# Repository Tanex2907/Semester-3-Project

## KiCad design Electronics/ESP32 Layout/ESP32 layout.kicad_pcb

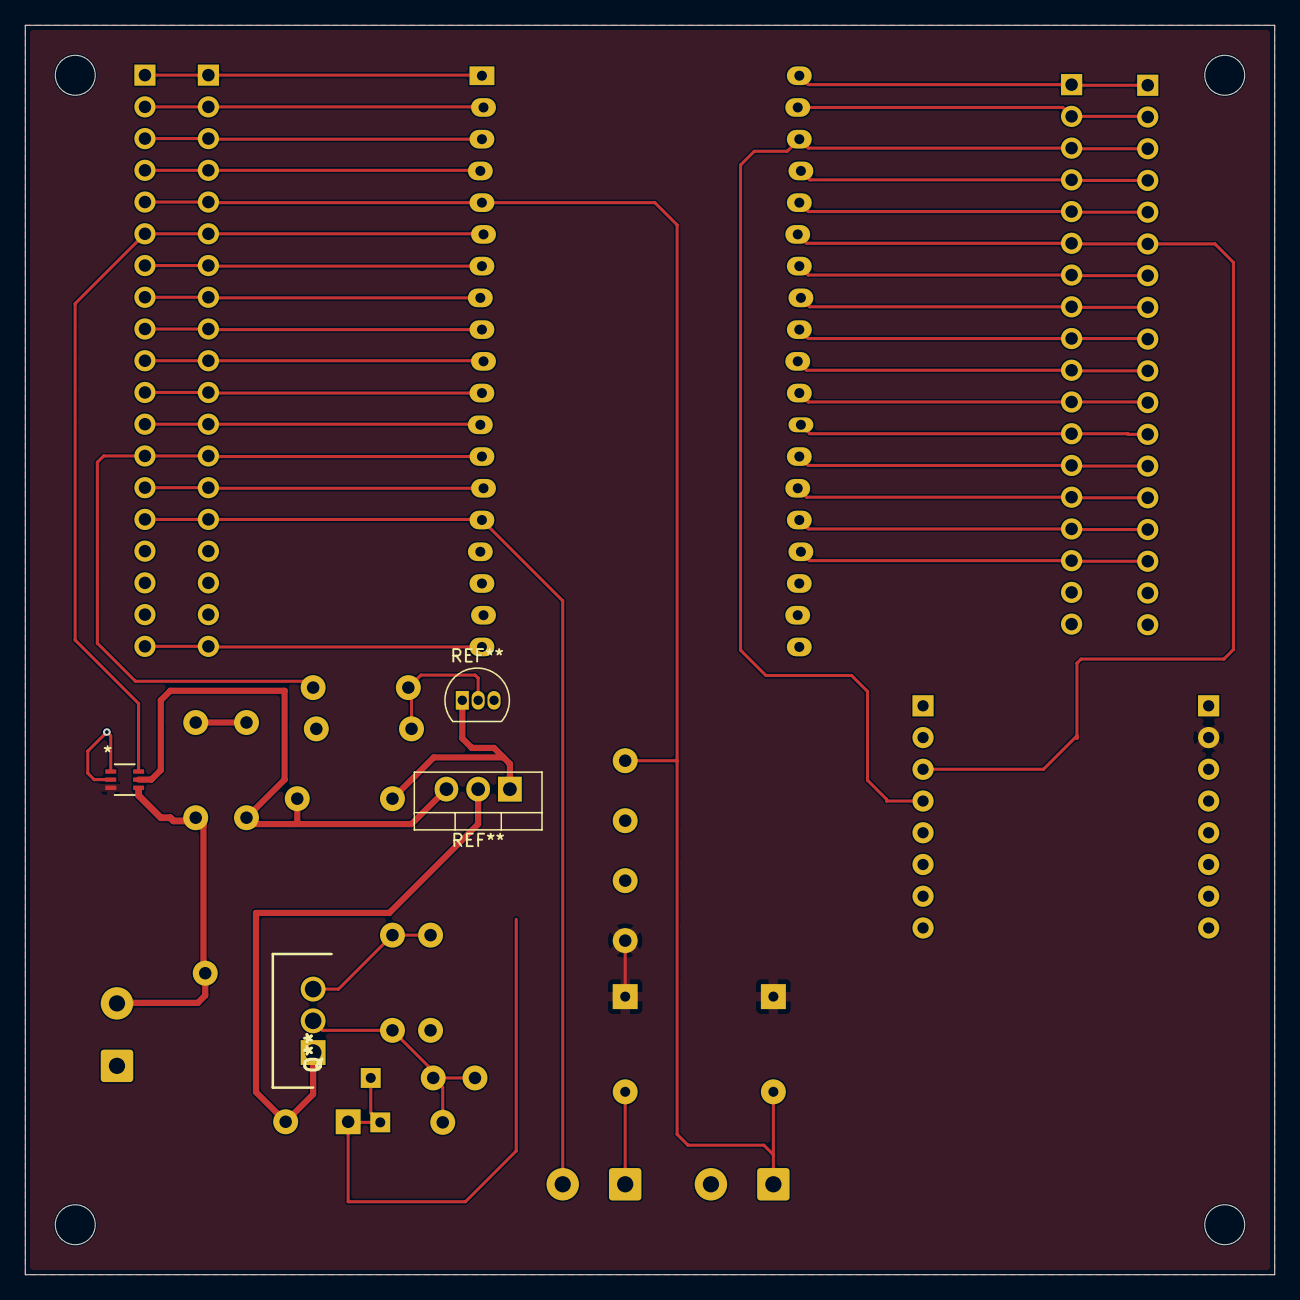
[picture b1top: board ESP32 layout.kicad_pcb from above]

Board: 2 copper layers, 100.0 x 100.0 mm, 24 parts (0 on the bottom side), 10 nets.

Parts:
C1, C3: 100u; C_Disc_D5.0mm_W2.5mm_P5.00mm
C2: 10u; C_Disc_D5.0mm_W2.5mm_P5.00mm
H1, H2, H3, H4: MountingHole_3.2mm_M3
J1: IR_LED (OPB100-EZ); TerminalBlock_Phoenix_MKDS-1,5-2_1x02_P5.00mm_Horizontal
J2: IR_SENSOR (OPB100-SZ); TerminalBlock_Phoenix_MKDS-1,5-2_1x02_P5.00mm_Horizontal
Q**: LM317T
R1, R1#2, R1#3, R3: 240; R_Axial_DIN0207_L6.3mm_D2.5mm_P7.62mm_Horizontal
R2: 390; R_Axial_DIN0207_L6.3mm_D2.5mm_P7.62mm_Horizontal
R4, R7: 10k; R_Axial_DIN0207_L6.3mm_D2.5mm_P7.62mm_Horizontal
R5, R6: 100; R_Axial_DIN0207_L6.3mm_D2.5mm_P7.62mm_Horizontal
TP1, TP2, TP3, TP4, TP5: TestPoint; TestPoint_THTPad_D2.0mm_Drill1.0mm

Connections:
3.3V: R6.1, R7.1, TP1.1
12V: C3.2, Q**.1, R1.2, TP2.1
GATE: R4.2, R5.1, R5.2
GND: C1.1, C2.1, C3.e, J2.2, R2.2, R4.1, TP3.1, TP4.1
IR_LED_A: J1.1, R6.2
IR_SENSE: J2.1, R7.2, TP5.1
LM317ADJUST: Q**.3, R1#2.1, R2.1
LM317OUT: C1.2, C2.2, Q**.2, R1#2.2
Shunt-: R1#3.2, R3.1
rshunt: R1.1, R1#3.1
